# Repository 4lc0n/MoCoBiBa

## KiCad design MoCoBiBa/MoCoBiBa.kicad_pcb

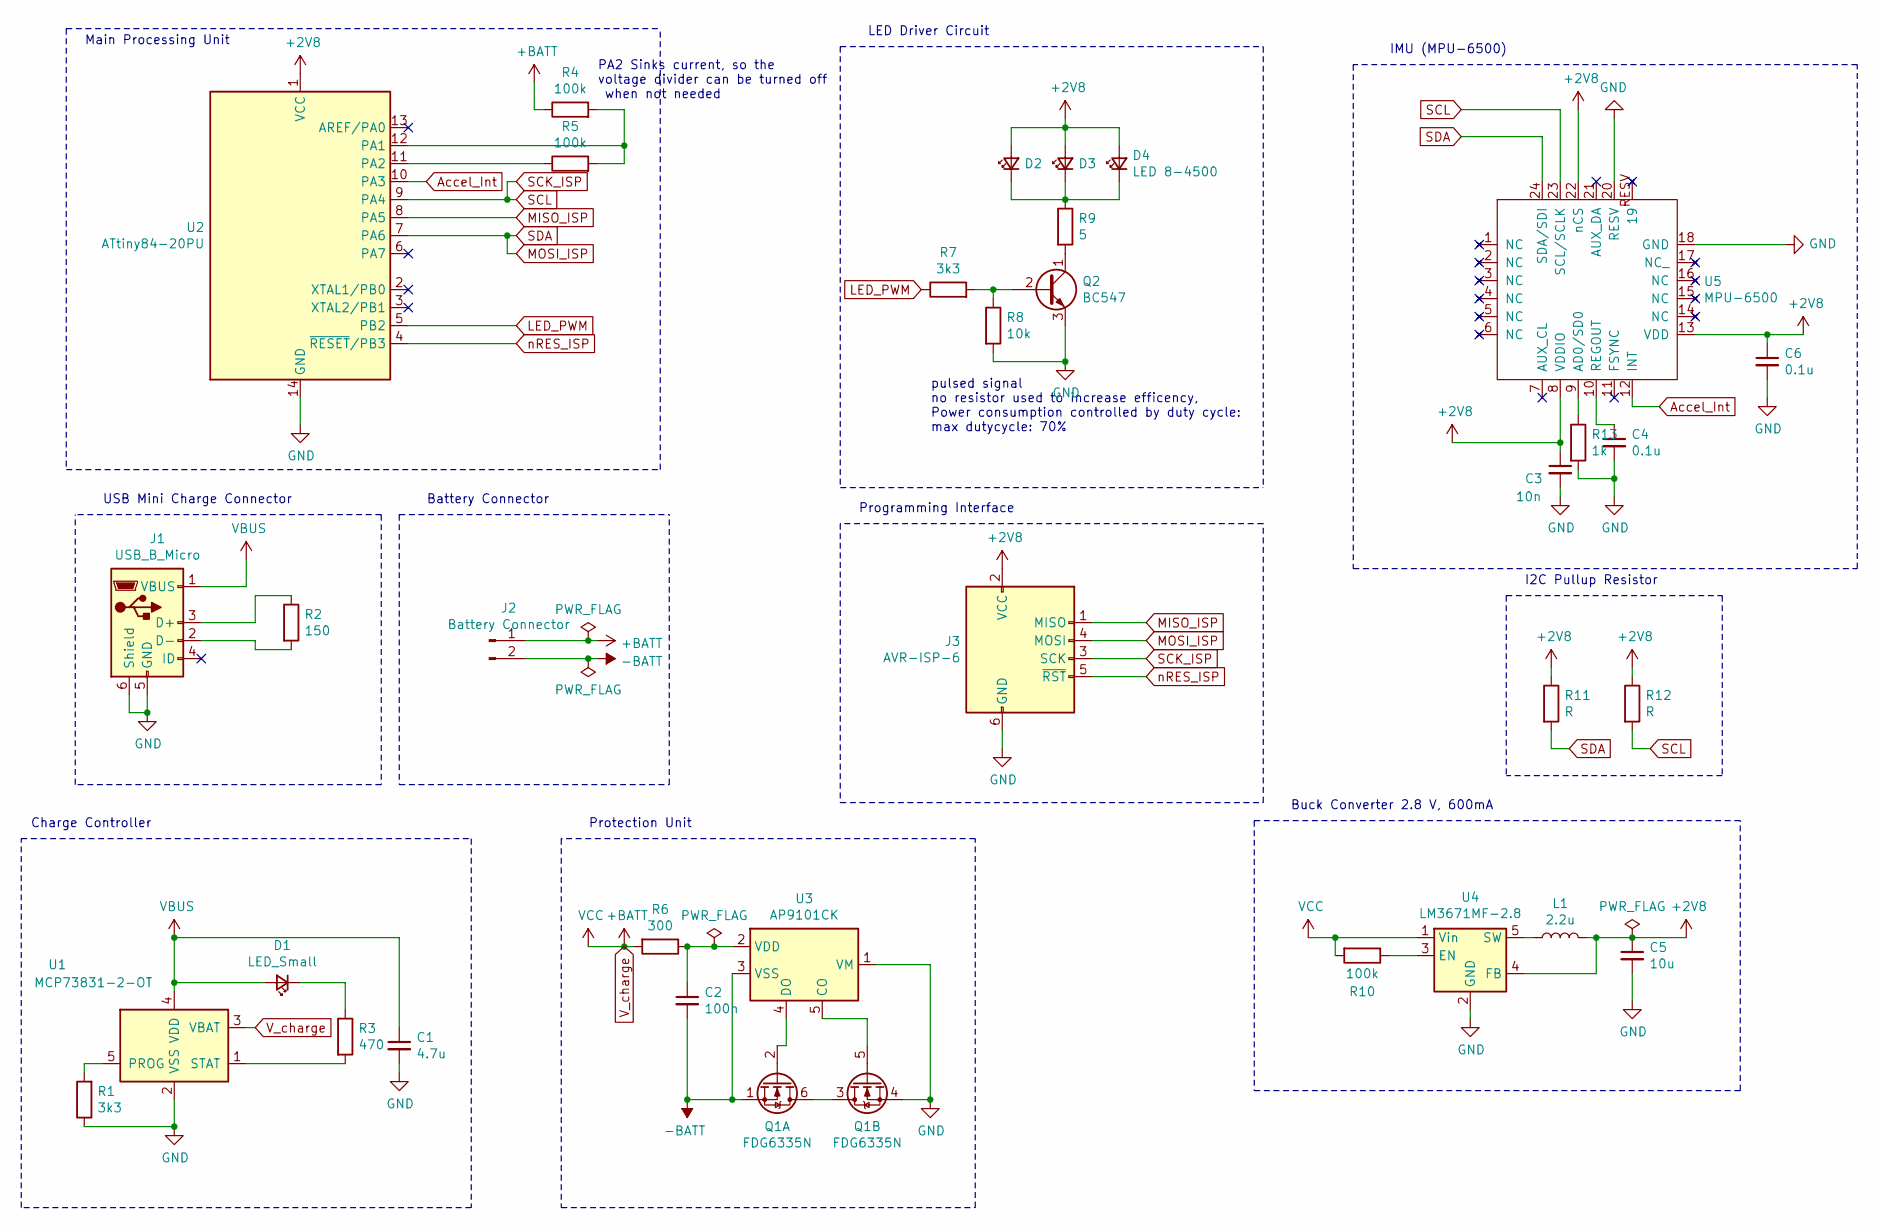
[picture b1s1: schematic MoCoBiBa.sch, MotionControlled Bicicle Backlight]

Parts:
C1: 4.7u; CP_Radial_D5.0mm_P2.00mm
C2: 100n; C_0805_2012Metric_Pad1.15x1.40mm_HandSolder
C3: 10n; C_Disc_D5.0mm_W2.5mm_P5.00mm
C4, C6: 0.1u; C_0805_2012Metric_Pad1.15x1.40mm_HandSolder
C5: 10u; CP_Radial_D5.0mm_P2.00mm
D1: LED_Small; LED_0805_2012Metric_Pad1.15x1.40mm_HandSolder
D2, D3, D4: LED 8-4500; LED_D8.0mm
J1: USB_B_Micro; USB_Mini-B_Wuerth_65100516121_Horizontal
J2: Battery Connector; PinSocket_1x02_P2.54mm_Vertical
J3: AVR-ISP-6; PinSocket_2x03_P2.54mm_Vertical
L1: 2.2u; L_0805_2012Metric_Pad1.15x1.40mm_HandSolder
Q1: FDG6335N; SOT-363_SC-70-6
Q2: BC547; TO-92_Inline
R1, R7: 3k3; R_0805_2012Metric_Pad1.15x1.40mm_HandSolder
R2: 150; R_0805_2012Metric_Pad1.15x1.40mm_HandSolder
R3: 470; R_0805_2012Metric_Pad1.15x1.40mm_HandSolder
R4, R5, R10: 100k; R_0805_2012Metric_Pad1.15x1.40mm_HandSolder
R6: 300; R_0805_2012Metric_Pad1.15x1.40mm_HandSolder
R8: 10k; R_0805_2012Metric_Pad1.15x1.40mm_HandSolder
R9: 5; R_0815_2038Metric_Pad1.53x4.00mm_HandSolder
R11, R12: R; R_0815_2038Metric_Pad1.53x4.00mm_HandSolder
R13: 1k; R_0805_2012Metric_Pad1.15x1.40mm_HandSolder
U1: MCP73831-2-OT; SOT-23-5
U2: ATtiny84-20PU; DIP-14_W7.62mm
U3: AP9101CK; SOT-23-5
U4: LM3671MF-2.8; TSOT-23-5
U5: MPU-6500; InvenSense_QFN-24_3x3mm_P0.4mm

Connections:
+2V8: C3.1, C5.1, C6.1, D2.2 (A), D3.2 (A), D4.2 (A), J3.2 (VCC), L1.2, R11.1, R12.1, U2.1 (VCC), U4.4 (FB), U5.8 (VDDIO), U5.13 (VDD), U5.22 (nCS)
-BATT: C2.2, J2.2, Q1.1 (S), U3.3 (VSS)
Accel_Int: U2.10 (PA3), U5.12 (INT)
GND: C1.2, C3.2, C4.2, C5.2, C6.2, J1.5 (GND), J1.6 (Shield), J3.6 (GND), Q1.4 (S), Q2.3 (E), R1.1, R8.2, R13.2, U1.2 (VSS), U2.14 (GND), U3.1 (VM), U4.2 (GND), U5.18 (GND), U5.20 (RESV)
LED_PWM: R7.1, U2.5 (PB2)
MISO_ISP: J3.1 (MISO), U2.8 (PA5)
MOSI_ISP: J3.4 (MOSI), R11.2, U2.7 (PA6), U5.24 (SDA/SDI)
unnamed: C2.1, R6.1, U3.2 (VDD)
unnamed: C4.1, U5.10 (REGOUT)
unnamed: D1.1 (K), R3.1
unnamed: D2.1 (K), D3.1 (K), D4.1 (K), R9.1
unnamed: J1.2 (D-), R2.2
unnamed: J1.3 (D+), R2.1
unnamed: L1.1, U4.5 (SW)
unnamed: Q1.2 (G), U3.4 (DO)
unnamed: Q1.3 (D), Q1.6 (D)
unnamed: Q1.5 (G), U3.5 (CO)
unnamed: Q2.1 (C), R9.2
unnamed: Q2.2 (B), R7.2, R8.1
unnamed: R1.2, U1.5 (PROG)
unnamed: R3.2, U1.1 (STAT)
unnamed: R4.2, R5.2, U2.12 (PA1)
unnamed: R5.1, U2.11 (PA2)
unnamed: R10.1, U4.3 (EN)
unnamed: R13.1, U5.9 (AD0/SD0)
SCK_ISP: J3.3 (SCK), R12.2, U2.9 (PA4), U5.23 (SCL/SCLK)
VBUS: C1.1, D1.2 (A), J1.1 (VBUS), U1.4 (VDD)
V_charge: J2.1, R4.1, R6.2, R10.2, U1.3 (VBAT), U4.1 (Vin)
nRES_ISP: J3.5 (~RST), U2.4 (~RESET~/PB3)

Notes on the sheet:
Charge Controller
Protection Unit
pulsed signal no resistor used to increase efficency, Power consumption controlled by duty cycle: max dutycycle: 70%
Buck Converter 2.8 V, 600mA
USB Mini Charge Connector
Battery Connector
Main Processing Unit
LED Driver Circuit
IMU (MPU-6500)
Programming Interface
I2C Pullup Resistor
PA2 Sinks current, so the voltage divider can be turned off when not needed

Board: 2 copper layers, 34 parts (0 on the bottom side), 29 nets, no tracks yet.

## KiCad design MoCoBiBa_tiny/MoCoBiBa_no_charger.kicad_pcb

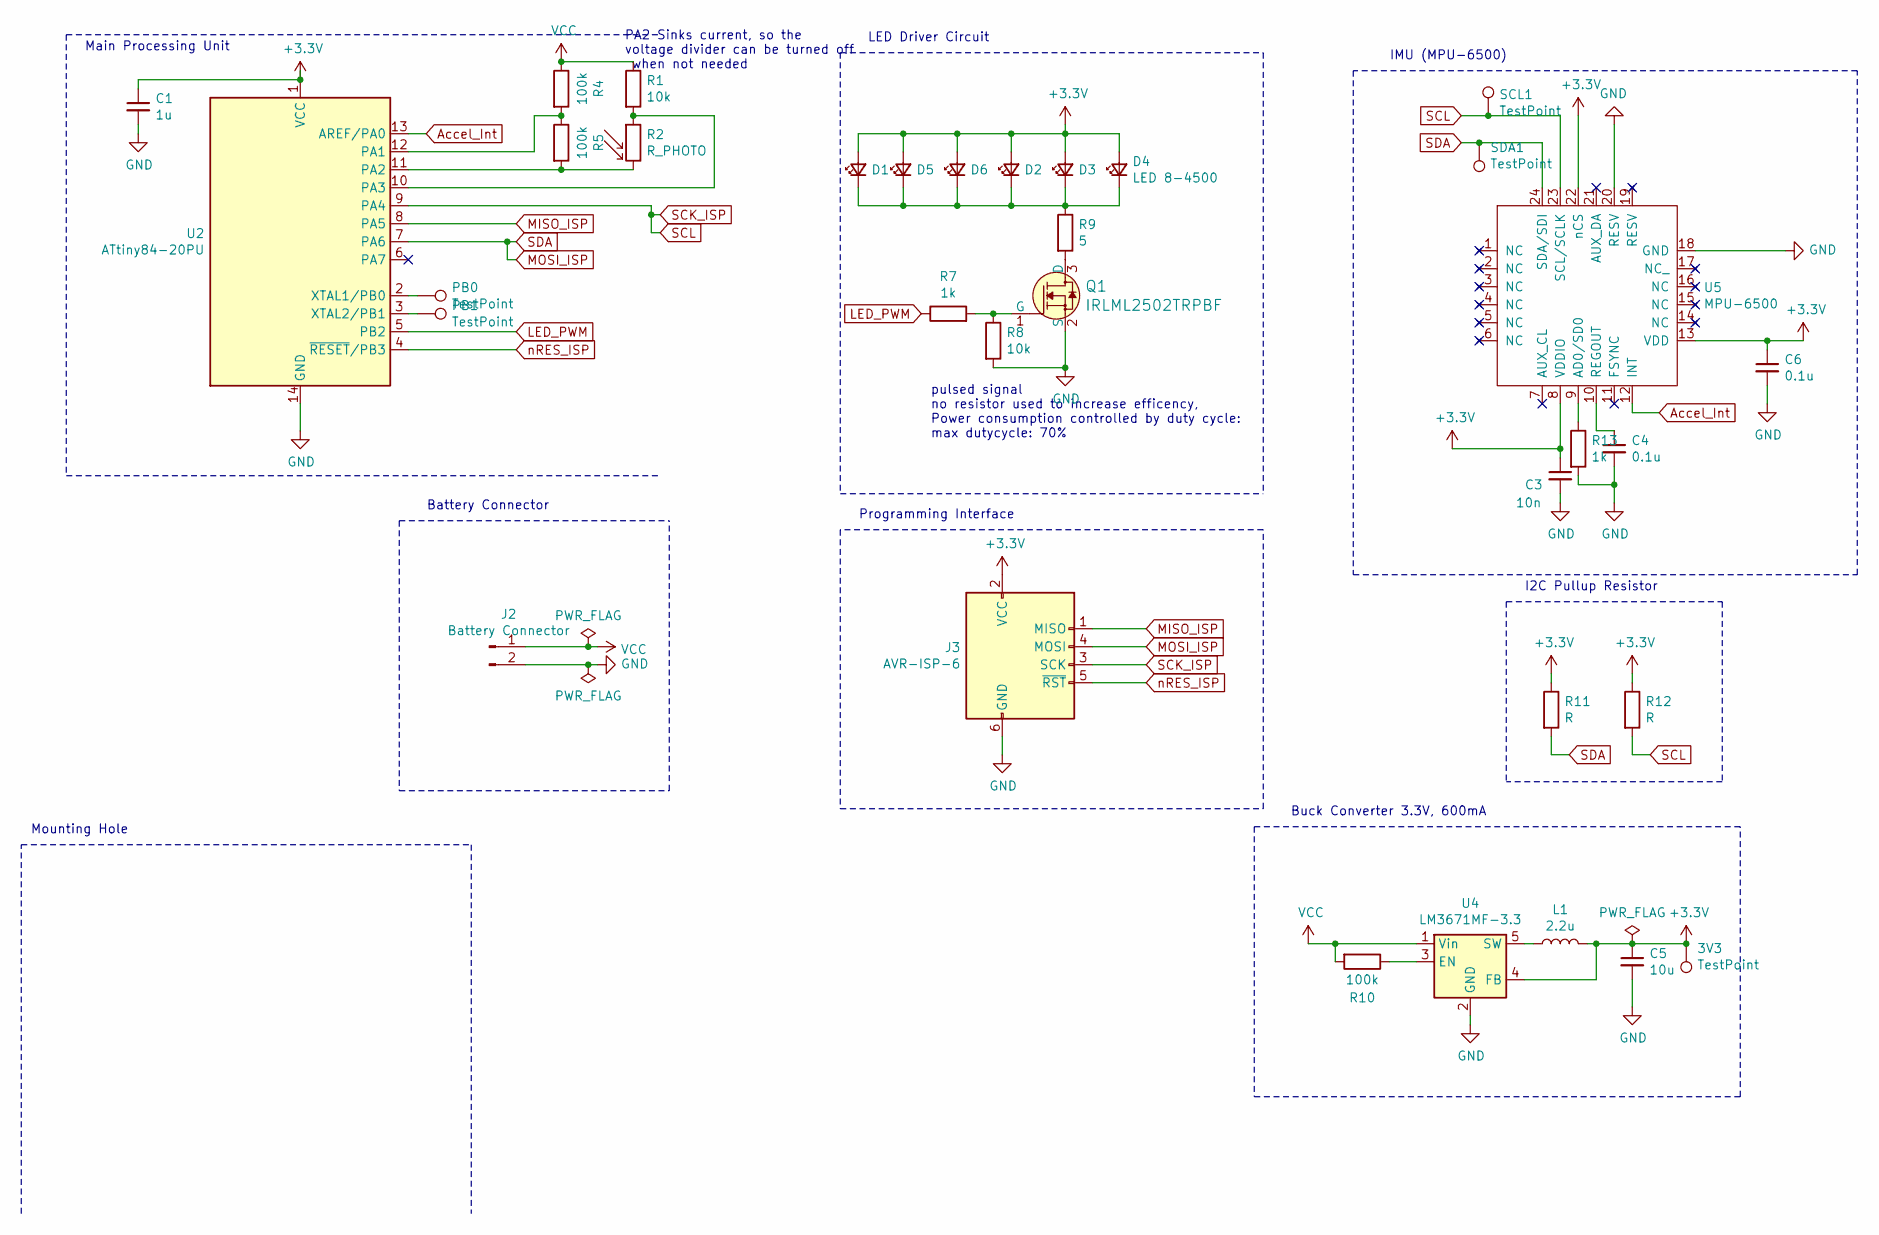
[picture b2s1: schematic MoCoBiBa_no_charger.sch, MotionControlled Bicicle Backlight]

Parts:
3V3: TestPoint; TestPoint_Pad_D1.5mm
C1: 1u; C_0805_2012Metric_Pad1.15x1.40mm_HandSolder
C3: 10n; C_0805_2012Metric_Pad1.15x1.40mm_HandSolder
C4, C6: 0.1u; C_0805_2012Metric_Pad1.15x1.40mm_HandSolder
C5: 10u; C_0805_2012Metric_Pad1.15x1.40mm_HandSolder
D1, D2, D3, D4, D5, D6: LED 8-4500; LED_PLCC-2
J2: Battery Connector; PinSocket_1x02_P2.54mm_Vertical
J3: AVR-ISP-6; PinSocket_2x03_P2.54mm_Vertical
L1: 2.2u; L_0805_2012Metric_Pad1.15x1.40mm_HandSolder
PB0, PB1: TestPoint; TestPoint_Pad_D1.5mm
Q1: IRLML2502TRPBF; SOT-23-3; MPN IRLML2502TRPBF; Digi-Key_PN IRLML2502TRPBFCT-ND
R1, R8: 10k; R_0805_2012Metric_Pad1.15x1.40mm_HandSolder
R2: R_PHOTO; R_Axial_DIN0204_L3.6mm_D1.6mm_P2.54mm_Vertical
R4, R5, R10: 100k; R_0805_2012Metric_Pad1.15x1.40mm_HandSolder
R7, R13: 1k; R_0805_2012Metric_Pad1.15x1.40mm_HandSolder
R9: 5; R_0815_2038Metric_Pad1.53x4.00mm_HandSolder
R11, R12: R; R_0805_2012Metric_Pad1.15x1.40mm_HandSolder
SCL1: TestPoint; TestPoint_Pad_D1.5mm
SDA1: TestPoint; TestPoint_Pad_D1.5mm
U2: ATtiny84-20PU; SOIC-14_3.9x8.7mm_P1.27mm
U4: LM3671MF-3.3; TSOT-23-5
U5: MPU-6500; InvenSense_QFN-24_3x3mm_P0.4mm

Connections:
+3V3: 3V3.1, C1.1, C3.1, C5.1, C6.1, D1.2 (A), D2.2 (A), D3.2 (A), D4.2 (A), D5.2 (A), D6.2 (A), J3.2 (VCC), L1.2, R11.1, R12.1, U2.1 (VCC), U4.4 (FB), U5.8 (VDDIO), U5.13 (VDD), U5.22 (nCS)
Accel_Int: U2.13 (AREF/PA0), U5.12 (INT)
GND: C1.2, C3.2, C4.2, C5.2, C6.2, J2.2, J3.6 (GND), Q1.2 (S), R8.2, R13.2, U2.14 (GND), U4.2 (GND), U5.18 (GND), U5.20 (RESV)
LED_PWM: R7.1, U2.5 (PB2)
MISO_ISP: J3.1 (MISO), U2.8 (PA5)
MOSI_ISP: J3.4 (MOSI), R11.2, SDA1.1, U2.7 (PA6), U5.24 (SDA/SDI)
unnamed: C4.1, U5.10 (REGOUT)
unnamed: D1.1 (K), D2.1 (K), D3.1 (K), D4.1 (K), D5.1 (K), D6.1 (K), R9.1
unnamed: L1.1, U4.5 (SW)
unnamed: PB0.1, U2.2 (XTAL1/PB0)
unnamed: PB1.1, U2.3 (XTAL2/PB1)
unnamed: Q1.1 (G), R7.2, R8.1
unnamed: Q1.3 (D), R9.2
unnamed: R1.2, R2.1, U2.10 (PA3)
unnamed: R2.2, R5.2, U2.11 (PA2)
unnamed: R4.2, R5.1, U2.12 (PA1)
unnamed: R10.1, U4.3 (EN)
unnamed: R13.1, U5.9 (AD0/SD0)
SCK_ISP: J3.3 (SCK), R12.2, SCL1.1, U2.9 (PA4), U5.23 (SCL/SCLK)
VCC: J2.1, R1.1, R4.1, R10.2, U4.1 (Vin)
nRES_ISP: J3.5 (~RST), U2.4 (~RESET~/PB3)

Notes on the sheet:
Mounting Hole
pulsed signal no resistor used to increase efficency, Power consumption controlled by duty cycle: max dutycycle: 70%
Buck Converter 3.3V, 600mA
Battery Connector
Main Processing Unit
LED Driver Circuit
IMU (MPU-6500)
Programming Interface
I2C Pullup Resistor
PA2 Sinks current, so the voltage divider can be turned off when not needed

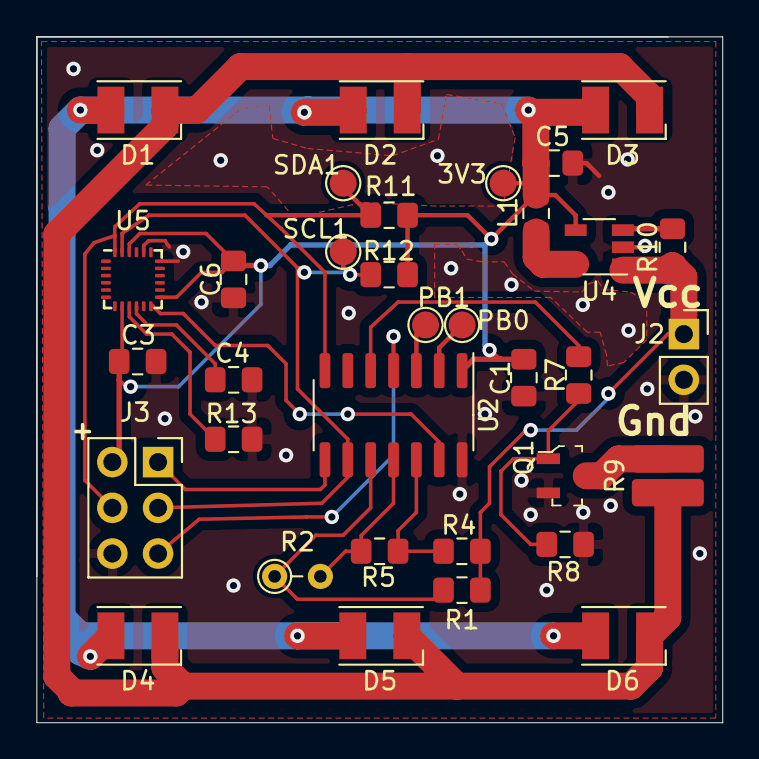
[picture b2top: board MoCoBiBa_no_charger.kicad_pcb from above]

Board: 2 copper layers, 38.1 x 38.1 mm, 34 parts (0 on the bottom side), 21 nets.

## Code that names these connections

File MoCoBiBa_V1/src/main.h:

#ifndef MAIN_H
#define MAIN_H

#include <stdint.h>
#include <stdbool.h>





#define DEBUG0 PB0
#define DEBUG0_PORT PORTB
#define DEBUG0_DDR DDRB
#define DEBUG1 PB1
#define DEBUG1_PORT PORTB
#define DEBUG1_DDR DDRB
#define LED PB2
#define LED_PORT PORTB
#define LED_DDR DDRB
#define LED_PIN PINB

#define ACC_INT PA0
#define ACC_INT_PORT PORTA
#define ACC_INT_DDR DDRA
#define ACC_INT_PIN PINA

#define V_BATT PA1
#define V_BATT_PIN PINA
#define V_BATT_PORT PORTA
#define V_BATT_DDR DDRA
#define V_SINK PA2
#define V_SINK_PIN PINA
#define V_SINK_PORT PORTA
#define V_SINK_DDR DDRA
#define V_LIGHT PA3
#define V_LIGHT_PIN PINA
#define V_LIGHT_PORT PORTA
#define V_LIGHT_DDR DDRA





// definitions for configuration

#define DARKNESS_THRESHHOLD_UPPER 512
#define DARKNESS_THRESHHOLD_LOWER 440

#define MOTION_THRESHHOLD         0.2

#define MOTION_TIMEOUT            60



#endif

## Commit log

2020-11-23 added writedown
2020-11-24 added MoCoBiBa_V1 Project * added PlatformIO MoCoBiBa_V1 Project * modified Attiny84_Test
2020-11-30 added power_consumption calculation, brightness readout * power_consumptoin.ods spreadsheet with consumption calculation from MPU-6500 and AtTiny84 Datasheet * writedown with programm thoughts * writ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
2020-12-01 minor changes to programm flow
2020-12-02 added PCINT and State Machine * Pin Change Interrupt with setup and deactivate implemented * fixed bug on no TWI after sleep
2021-01-04 added FIR Filter Files from t-filter.engineerjs.com and separated MPU functions
